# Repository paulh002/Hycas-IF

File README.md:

# Hycas-IF
Hycas IF amplifier inclusive product detector, s-meter and audio amp

This is my take on the well know W7ZOI hycas if amplifier. I made several versions one through the whole and after that SMD using mostly 1206 SMD components. Check the footprints for details because sometime the kicad libraries are not very consistant creating issues with ordering the wrong components (The diodes were 323 instead of DO-23 so needed to order again).
I included the s-meter extension which works very well. There are some resistors which may need some tuning depending on how much gain you want to achieve (I changed R17 to 1K instead of 3.3k to reduce the hiss, also R25 270 Ohm I needed to reduce to 47 Ohm the get the AVC responding faster in the shared kicad pcb layout it is now a potmeter)
For audio amplifier it uses a TDA 2003 which is driven by a small pre-amp. The input of the pre-amp is shortend with 100NF to supress HF into the audio stage.

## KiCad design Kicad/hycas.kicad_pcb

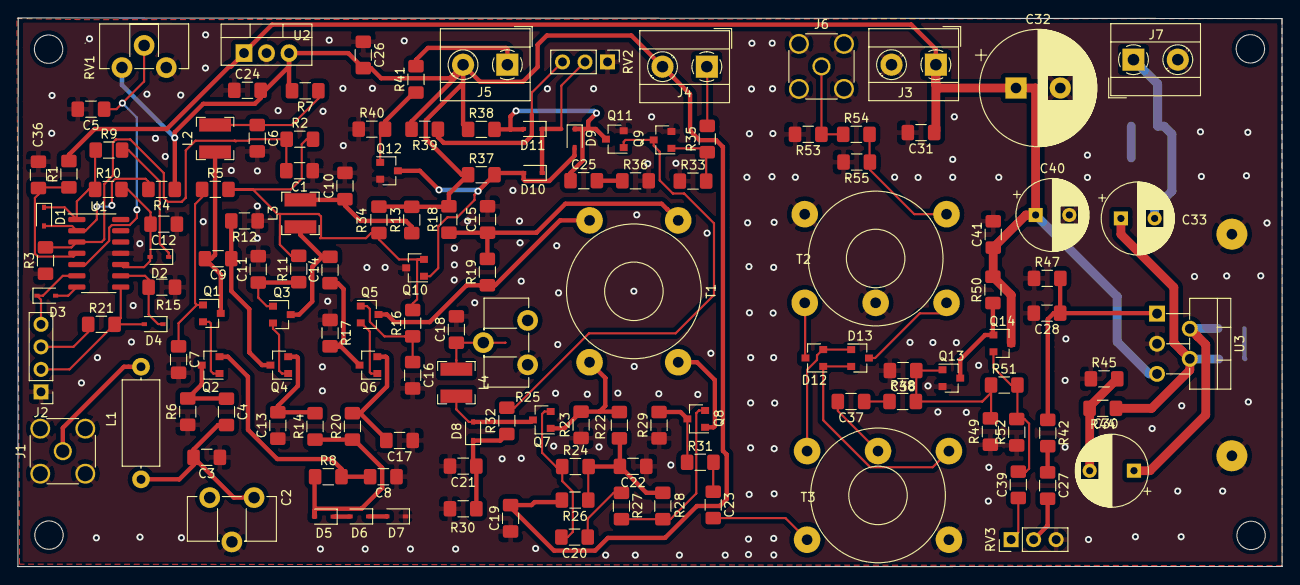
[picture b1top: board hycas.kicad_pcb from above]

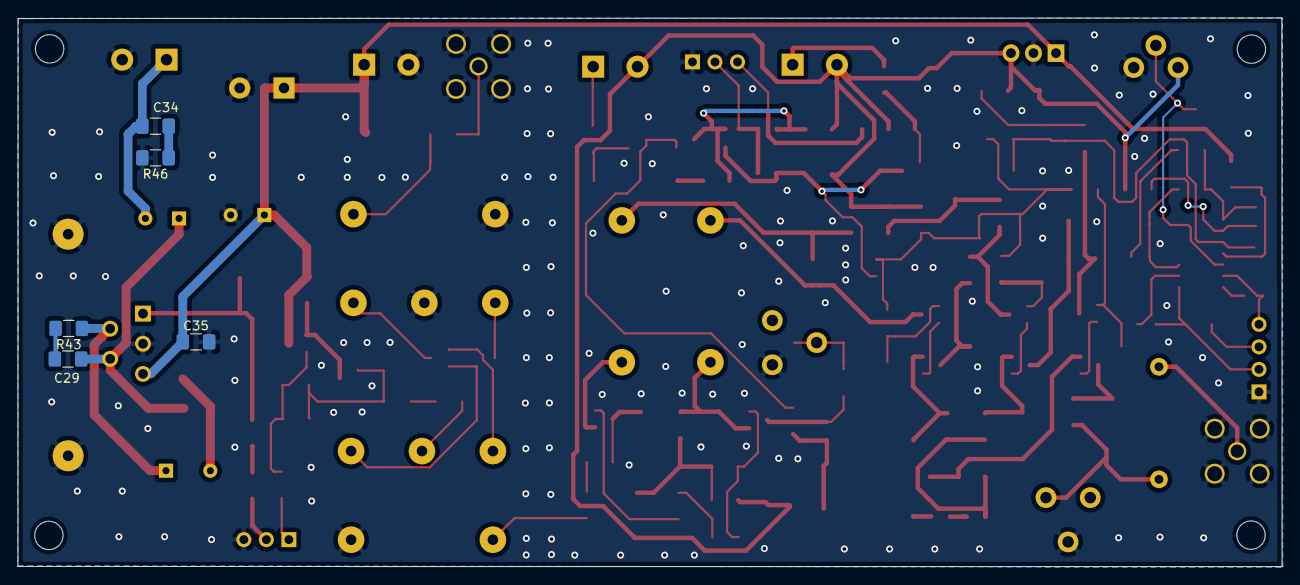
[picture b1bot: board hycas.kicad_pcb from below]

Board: 2 copper layers, 142.6 x 61.9 mm, 149 parts (5 on the bottom side), 82 nets.

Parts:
 : SolderWirePad_1x01_Drill1.2mm
 #2: SolderWirePad_1x01_Drill1.2mm
 #3,  #4,  #5,  #6: MountingHole_3.2mm_M3
C1, C5, C6, C8, C10, C13, C15, C17, C18, C19, C20, C22, C23, C26, C34, C36: 0.1u; C_1206_3216Metric_Pad1.42x1.75mm_HandSolder
C2: C_Variable; Potentiometer_ACP_CA9-H5_Horizontal
C3, C4, C7, C9, C11, C14, C16, C21: 0.01u; C_1206_3216Metric_Pad1.42x1.75mm_HandSolder
C12, C25: 4.7u; C_1206_3216Metric_Pad1.42x1.75mm_HandSolder
C24: 10u; C_1206_3216Metric_Pad1.42x1.75mm_HandSolder
C27, C37, C39: 1u; C_1206_3216Metric_Pad1.42x1.75mm_HandSolder
C28: 820p; C_1206_3216Metric_Pad1.42x1.75mm_HandSolder
C29: 39nf; C_1206_3216Metric_Pad1.42x1.75mm_HandSolder
C30: 470u; CP_Radial_D8.0mm_P5.00mm
C31, C35, C41: 100nf; C_1206_3216Metric_Pad1.42x1.75mm_HandSolder
C32: 2200u; CP_Radial_D13.0mm_P5.00mm
C33, C40: 470u; CP_Radial_D8.0mm_P3.80mm
C38: 100n; C_1206_3216Metric_Pad1.42x1.75mm_HandSolder
D1, D2, D3, D4, D5, D6, D7, D8: D; D_SOD-323
D9, D10, D11: 1N4148; D_SOD-323
D12, D13: BAT54S; SOT-23
J1: Conn_Coaxial; SMA_Amphenol_132134_Vertical
J2: S-Meter; PinHeader_1x04_P2.54mm_Vertical
J3: Vcc; TerminalBlock_MetzConnect_Type055_RT01502HDWU_1x02_P5.00mm_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
J4: AGC Off; TerminalBlock_MetzConnect_Type055_RT01502HDWU_1x02_P5.00mm_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
J5: Mute; TerminalBlock_MetzConnect_Type055_RT01502HDWU_1x02_P5.00mm_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
J6: BFO; SMA_Amphenol_132134_Vertical
J7: Speaker; TerminalBlock_MetzConnect_Type055_RT01502HDWU_1x02_P5.00mm_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
L1: 120m; L_Axial_L9.5mm_D4.0mm_P12.70mm_Horizontal_Fastron_SMCC
L2, L3, L4: 120m; L_Bourns-SRN4018
Q1, Q3, Q5, Q9, Q11, Q12: 2N3904; SOT-23
Q2, Q4, Q6: J310; SOT-23
Q7, Q8, Q10: 2N3906; SOT-23
Q13, Q14: 2N3904_SOT23; SOT-23
R1, R7, R13, R18: 100; R_1206_3216Metric_Pad1.42x1.75mm_HandSolder
R2, R23, R33, R35, R40, R41: 10k; R_1206_3216Metric_Pad1.42x1.75mm_HandSolder
R3: 1meg; R_1206_3216Metric_Pad1.42x1.75mm_HandSolder
R4: 22k; R_1206_3216Metric_Pad1.42x1.75mm_HandSolder
R5, R11, R16, R44: 220; R_1206_3216Metric_Pad1.42x1.75mm_HandSolder
R6: 3k; R_1206_3216Metric_Pad1.42x1.75mm_HandSolder
R8, R14, R20, R26: 180; R_1206_3216Metric_Pad1.42x1.75mm_HandSolder
R9, R22: 4.7k; R_1206_3216Metric_Pad1.42x1.75mm_HandSolder
R10, R15, R30, R47: 100k; R_1206_3216Metric_Pad1.42x1.75mm_HandSolder
R12, R17, R48, R49, R50: 1k; R_1206_3216Metric_Pad1.42x1.75mm_HandSolder
R19: 3.3k; R_1206_3216Metric_Pad1.42x1.75mm_HandSolder
R21: 5.1k; R_1206_3216Metric_Pad1.42x1.75mm_HandSolder
R24, R28: 680; R_1206_3216Metric_Pad1.42x1.75mm_HandSolder
R25: 270; Potentiometer_ACP_CA9-H5_Horizontal
R27: 22; R_1206_3216Metric_Pad1.42x1.75mm_HandSolder
R29: 51; R_1206_3216Metric_Pad1.42x1.75mm_HandSolder
R31, R36, R46: 1; R_1206_3216Metric_Pad1.42x1.75mm_HandSolder
R32, R39, R42: 2.2k; R_1206_3216Metric_Pad1.42x1.75mm_HandSolder
R34: 47k; R_1206_3216Metric_Pad1.42x1.75mm_HandSolder
R37, R38: 1.5meg; R_1206_3216Metric_Pad1.42x1.75mm_HandSolder
R43: 39; R_1206_3216Metric_Pad1.42x1.75mm_HandSolder
R45: 2.2; R_1206_3216Metric_Pad1.42x1.75mm_HandSolder
R51: 5k; R_1206_3216Metric_Pad1.42x1.75mm_HandSolder
R52: 500; R_1206_3216Metric_Pad1.42x1.75mm_HandSolder
R53, R55: 150; R_1206_3216Metric_Pad1.42x1.75mm_HandSolder
R54: 33; R_1206_3216Metric_Pad1.42x1.75mm_HandSolder
RV1: R_POT; Potentiometer_ACP_CA9-H2,5_Horizontal
RV2: 5k; PinHeader_1x03_P2.54mm_Vertical
RV3: 10k; PinHeader_1x03_P2.54mm_Vertical
T1: 16T 4T FB-43-2401; Transformer_Toroid_Horizontal_D14.0mm_Amidon-T50
T2, T3: T50-6; Transformer_Toroid_Horizontal_3S_D14.0mm_Amidon-T50
U1: LM324; SOIC-14_3.9x8.7mm_P1.27mm
U2: L7809; TO-220-3_Vertical
U3: TDA2003; TO-220-5_P3.4x3.7mm_StaggerOdd_Lead3.8mm_Vertical

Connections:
AGC: Q10.2, R2.2, R5.2, R11.2, R16.2, R34.2
GND: .1, #2.1, C1.1, C2.2, C3.1, C5.2, C6.2, C7.2, C8.1, C10.2, C11.2, C12.1, C13.1, C15.2, C16.2, C17.1, C18.2, C19.1, C21.2, C22.1, C24.1, C26.1, C28.2, C31.2, C32.2, C35.2, C36.1, C38.2, C40.2, C41.2, D7.1, J1.2, J2.1, J3.2, J6.2, J7.2, Q9.2, Q10.3, Q11.2, Q12.2, Q13.2, R3.1, R6.1, R12.1, R15.2, R17.1, R23.1, R25.1, R29.1, R30.1, R33.1, R36.2, R40.1, R45.1, R46.2, R47.1, R49.1, R52.1, R53.2, R55.2, RV1.3, RV2.1, RV3.3, T2.2, T2.4, T3.2, U1.11, U2.2, U3.3
IF: C23.2, T3.1
Mute: J5.1, R41.2
unnamed: C1.2, R2.1, R3.2, U1.3
unnamed: C2.1, C3.2, C4.2, L1.2
unnamed: C5.1, RV1.2, U1.5
unnamed: C7.1, Q1.1, R5.1
unnamed: C9.2, L2.2, Q1.3
unnamed: C10.1, L3.1, R13.1
unnamed: C11.1, Q3.1, R11.1
unnamed: C12.2, D2.2, R10.2, U1.10
unnamed: C13.2, Q4.2, R14.2
unnamed: C14.2, L3.2, Q3.3
unnamed: C15.1, R18.1, R19.2, T1.1
unnamed: C16.1, Q5.1, R16.1
unnamed: C17.2, Q6.2, R20.2
unnamed: C18.1, L4.2, R25.2
unnamed: C20.1, R27.1
unnamed: C20.2, Q7.2, R24.1
unnamed: C21.1, D8.1, R30.2, R32.1
unnamed: C22.2, R22.2, R24.2, R26.1, R28.2
unnamed: C23.1, R31.2
unnamed: C25.1, D9.1, D11.2, Q11.3, R38.2
unnamed: C25.2, R36.1
unnamed: C27.1, R42.2
unnamed: C27.2, RV3.2
unnamed: C28.1, R42.1, R47.2, U3.1
unnamed: C29.1, R43.2
unnamed: C29.2, C33.1, R44.1, U3.4
unnamed: C30.1, R43.1, U3.2
unnamed: C30.2, R44.2, R45.2
unnamed: C33.2, C34.2, J7.1
unnamed: C34.1, R46.1
unnamed: C36.2, R1.1, U1.4
unnamed: C37.1, R48.1
unnamed: C37.2, T3.4
unnamed: C38.1, Q13.1, R48.2, R49.2, R51.1
unnamed: C39.1, RV3.1
unnamed: C39.2, Q14.2, R51.2, R52.2
unnamed: D1.1, R9.1, R10.1, U1.1
unnamed: D1.2, R4.2, U1.2
unnamed: D2.1, R9.2
unnamed: D3.1, J2.4, U1.6
unnamed: D3.2, U1.7
unnamed: D4.1, R15.1, U1.9
unnamed: D4.2, J2.2, R21.2, U1.8
unnamed: D5.1, D6.2
unnamed: D6.1, D7.2
unnamed: D8.2, L4.1, Q7.3
unnamed: D10.1, D11.1, RV2.2
unnamed: D9.2, D10.2, Q10.1, Q12.3, R37.2
unnamed: D12.1, D13.2, T3.5
unnamed: D12.2, D13.1, T3.3
unnamed: D12.3, T2.5
unnamed: D13.3, T2.3
unnamed: J1.1, L1.1
unnamed: J2.3, R21.1
unnamed: J4.1, R35.2
unnamed: J6.1, R53.1, R54.1
unnamed: Q3.2, Q4.1
unnamed: Q5.2, Q6.1
unnamed: Q8.1, T1.3
unnamed: Q8.2, R27.2, R28.1
unnamed: Q8.3, R29.2, R31.1
unnamed: Q9.1, R33.2, R35.1
unnamed: Q9.3, Q11.1, R32.2
unnamed: Q12.1, R40.2, R41.1
unnamed: Q13.3, Q14.1, R50.1
unnamed: R39.1, RV2.3
unnamed: R54.2, R55.1, T2.1
V12v: C31.1, C32.1, C35.1, C40.1, C41.1, J3.1, Q14.3, R1.2, R50.2, U2.1, U3.5
VQ5: Q5.3, R19.1, T1.2
VSource: D5.2, R8.1, R14.1, R20.1
Vcc: C19.2, C24.2, C26.2, J4.2, J5.2, R4.1, R7.2, R13.2, R18.2, R26.2, R34.1, R37.1, R38.1, R39.2, RV1.1, U2.3
Vin2: R22.1, R23.2, T1.4
Vin-q2: C4.1, Q2.3, R6.2
Vin-q4: C9.1, Q4.3, R12.2
Vin-q6: C14.1, Q6.3, R17.2
vQ1: C6.1, L2.1, R7.1
vQ1Q2: Q1.2, Q2.1
vsQ1: C8.2, Q2.2, R8.2

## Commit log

2020-08-13 updated version
